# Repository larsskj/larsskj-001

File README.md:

A board for connecting TLC 5940 boards
======================================

### larsskj-001

This project is a PCB layout created in KiCAD for a board to connect one or more TLC 5940 LED controllers using ordinary IDC connectors and flat cable.

It's primarily intended for use in model railroading. The board has a wide edge with mounting holes, but can easily be cut to smaller dimensions if glued to the bottom of a structure or similar projects.

The board is shared at [OSH Park](https://oshpark.com/shared_projects/Qwm4SQ2z), where you can order copies.

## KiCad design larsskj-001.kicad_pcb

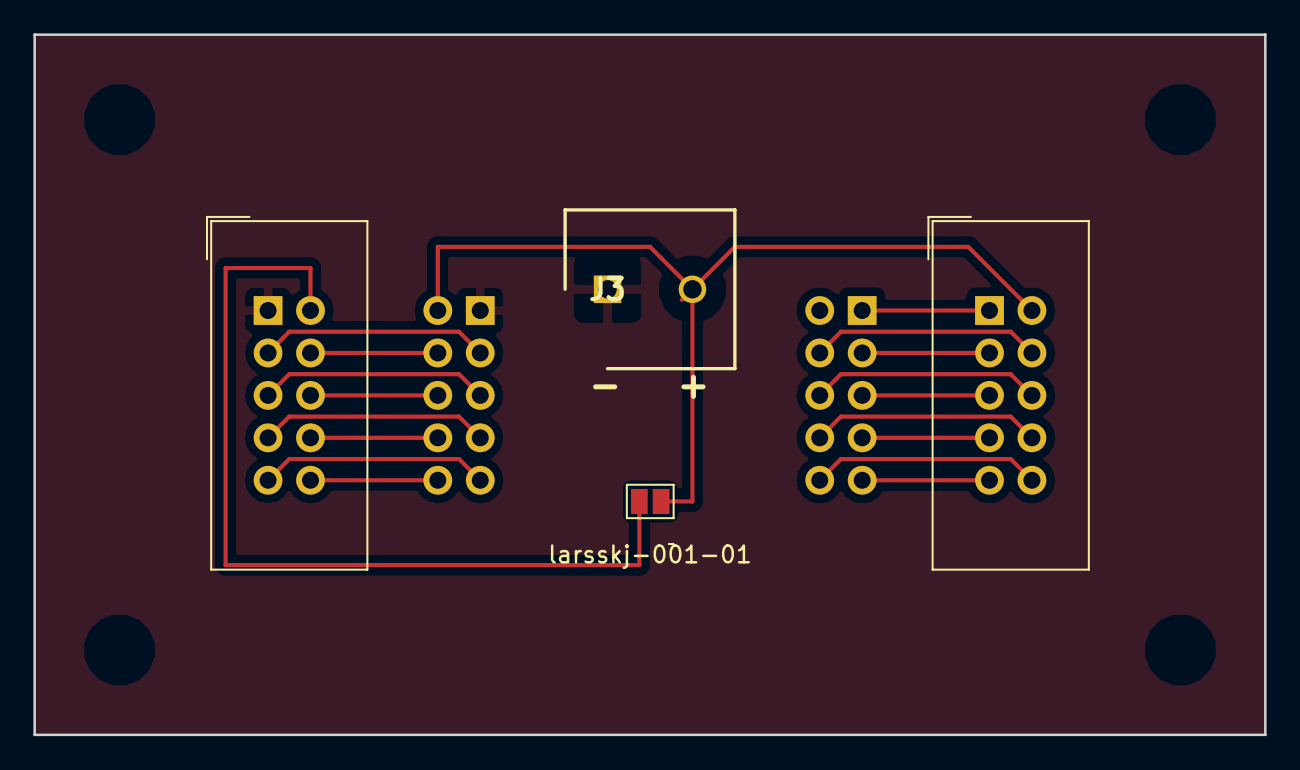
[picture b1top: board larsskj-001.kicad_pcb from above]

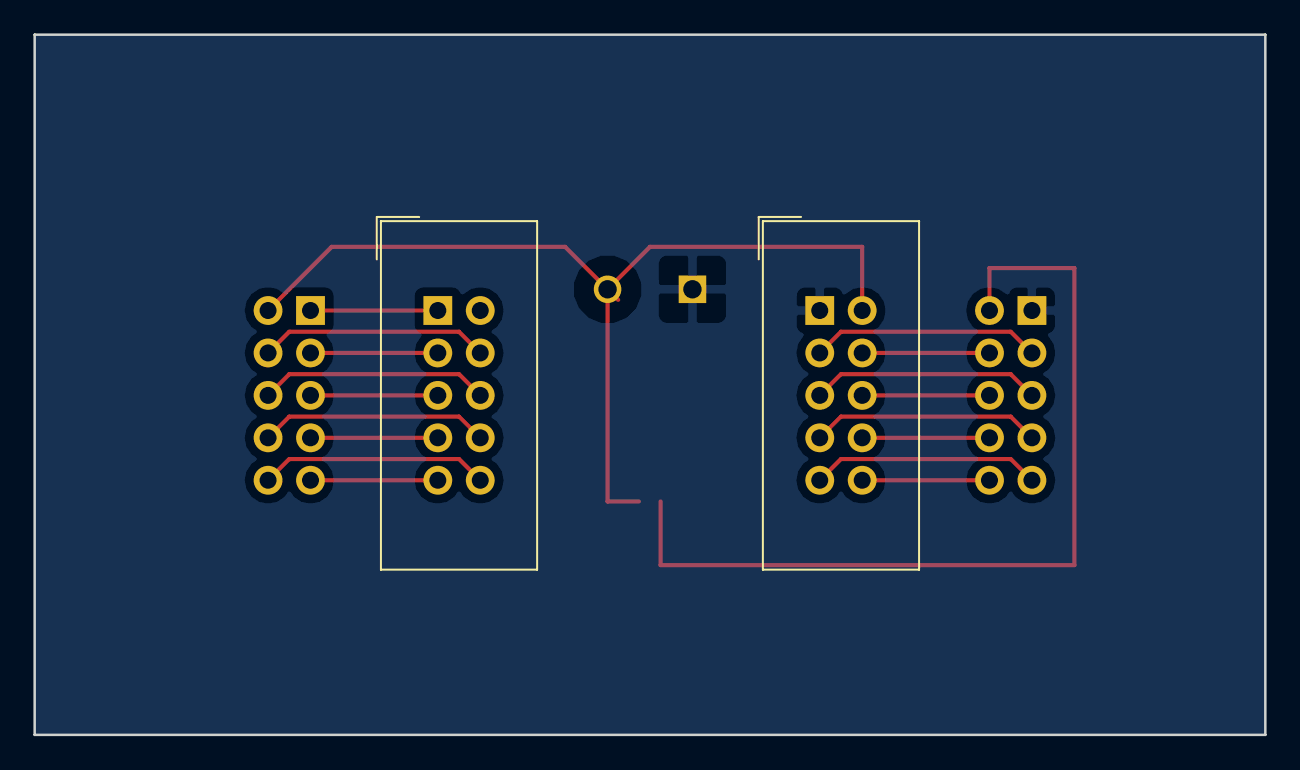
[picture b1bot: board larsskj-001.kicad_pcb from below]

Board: 2 copper layers, 73.7 x 41.9 mm, 6 parts (2 on the bottom side), 20 nets.

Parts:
J1: In; IDC-Header_2x05_P2.54mm_Vertical
J2: TLC in; IDC-Header_2x05_P2.54mm_Vertical
J3: 1888687; SHDR2W90P0X508_1X2_1016X950X1500P
J4: TLC out; IDC-Header_2x05_P2.54mm_Vertical
J5: Out; IDC-Header_2x05_P2.54mm_Vertical
JP1: VCC passthrough; SolderJumper-2_P1.3mm_Open_Pad1.0x1.5mm

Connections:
GND: J1.1, J2.1, J3.1
unnamed: J1.2, JP1.1
unnamed: J1.3, J2.3
unnamed: J1.4, J2.4
unnamed: J1.5, J2.5
unnamed: J1.6, J2.6
unnamed: J1.7, J2.7
unnamed: J1.8, J2.8
unnamed: J1.9, J2.9
unnamed: J1.10, J2.10
unnamed: J4.1, J5.1
unnamed: J4.3, J5.3
unnamed: J4.4, J5.4
unnamed: J4.5, J5.5
unnamed: J4.6, J5.6
unnamed: J4.7, J5.7
unnamed: J4.8, J5.8
unnamed: J4.9, J5.9
unnamed: J4.10, J5.10
VCC: J2.2, J3.2, J5.2, JP1.2

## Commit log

2019-03-24 Initial import
2019-03-24 Adding .gitignore
2019-03-24 README.md added
2019-03-24 README.md updated
2019-03-30 README.md modified
